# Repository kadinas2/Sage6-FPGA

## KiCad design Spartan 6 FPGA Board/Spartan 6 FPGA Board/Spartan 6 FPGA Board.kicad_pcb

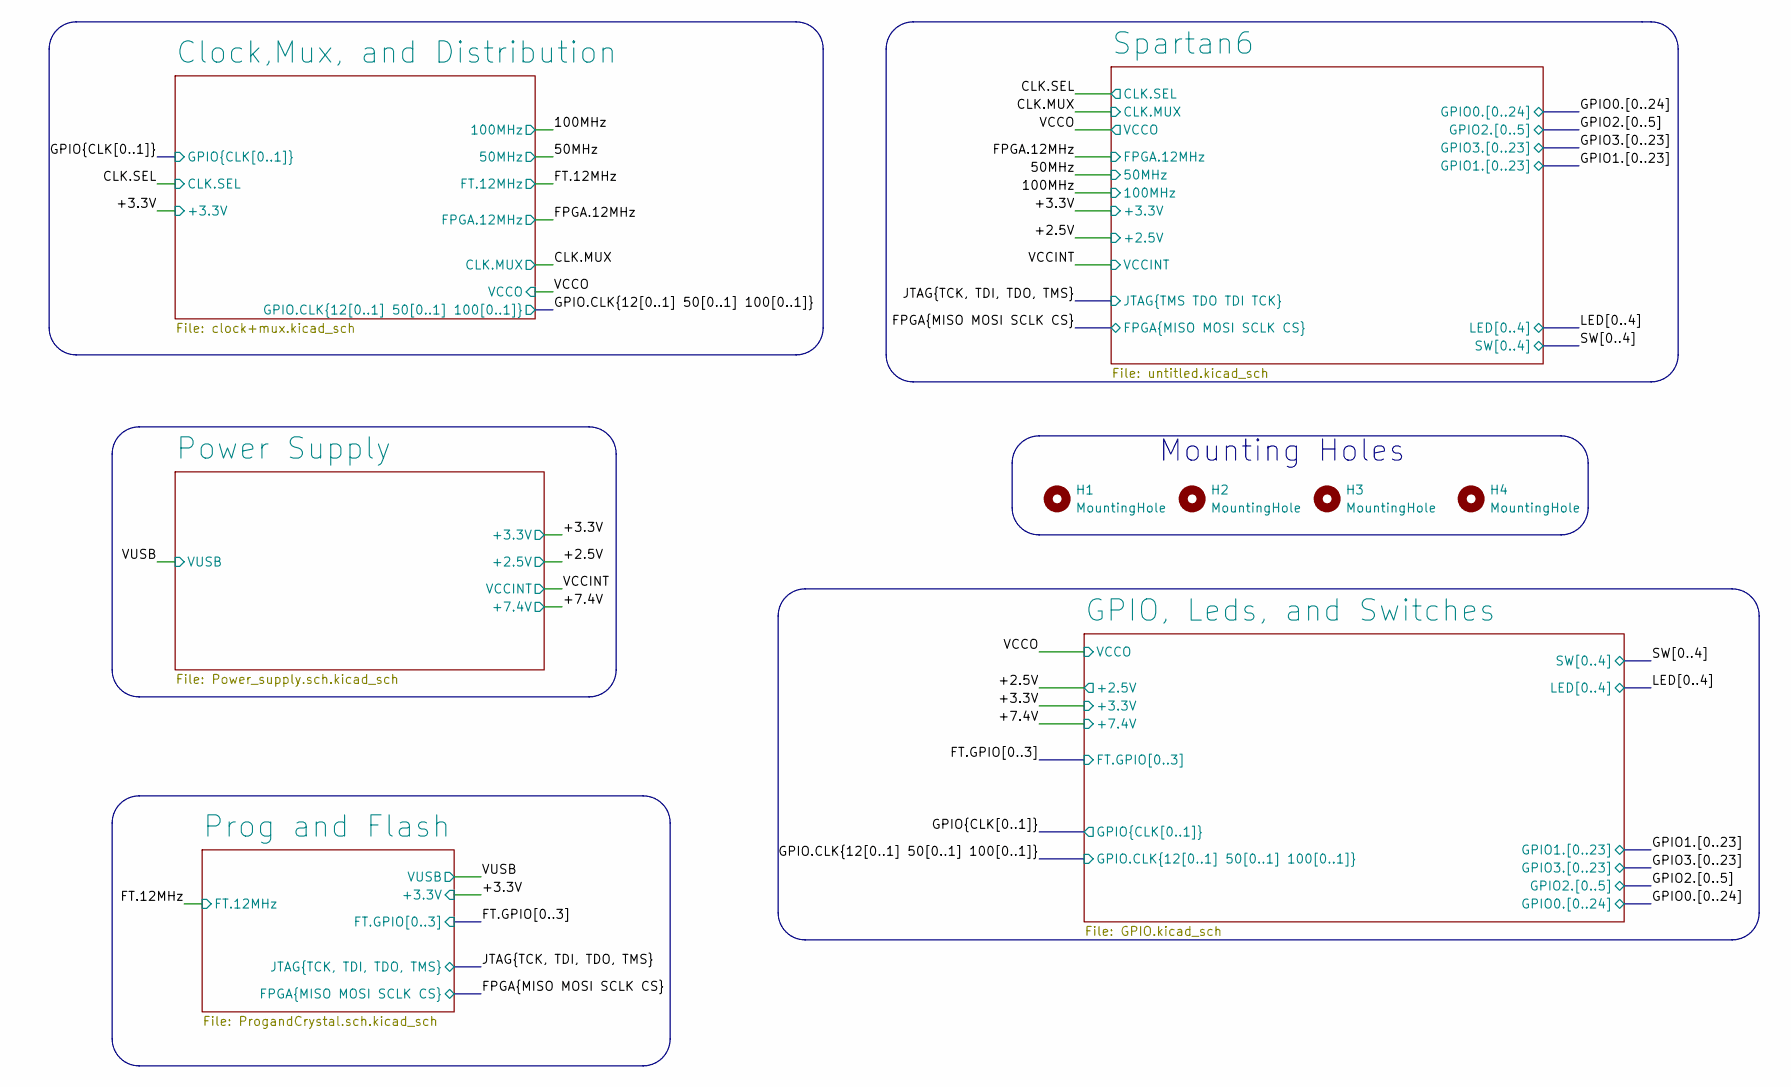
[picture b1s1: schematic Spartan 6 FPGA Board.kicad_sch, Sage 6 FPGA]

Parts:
H1, H2, H3, H4: MountingHole; MountingHole_2.2mm_M2

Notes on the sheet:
Mounting Holes

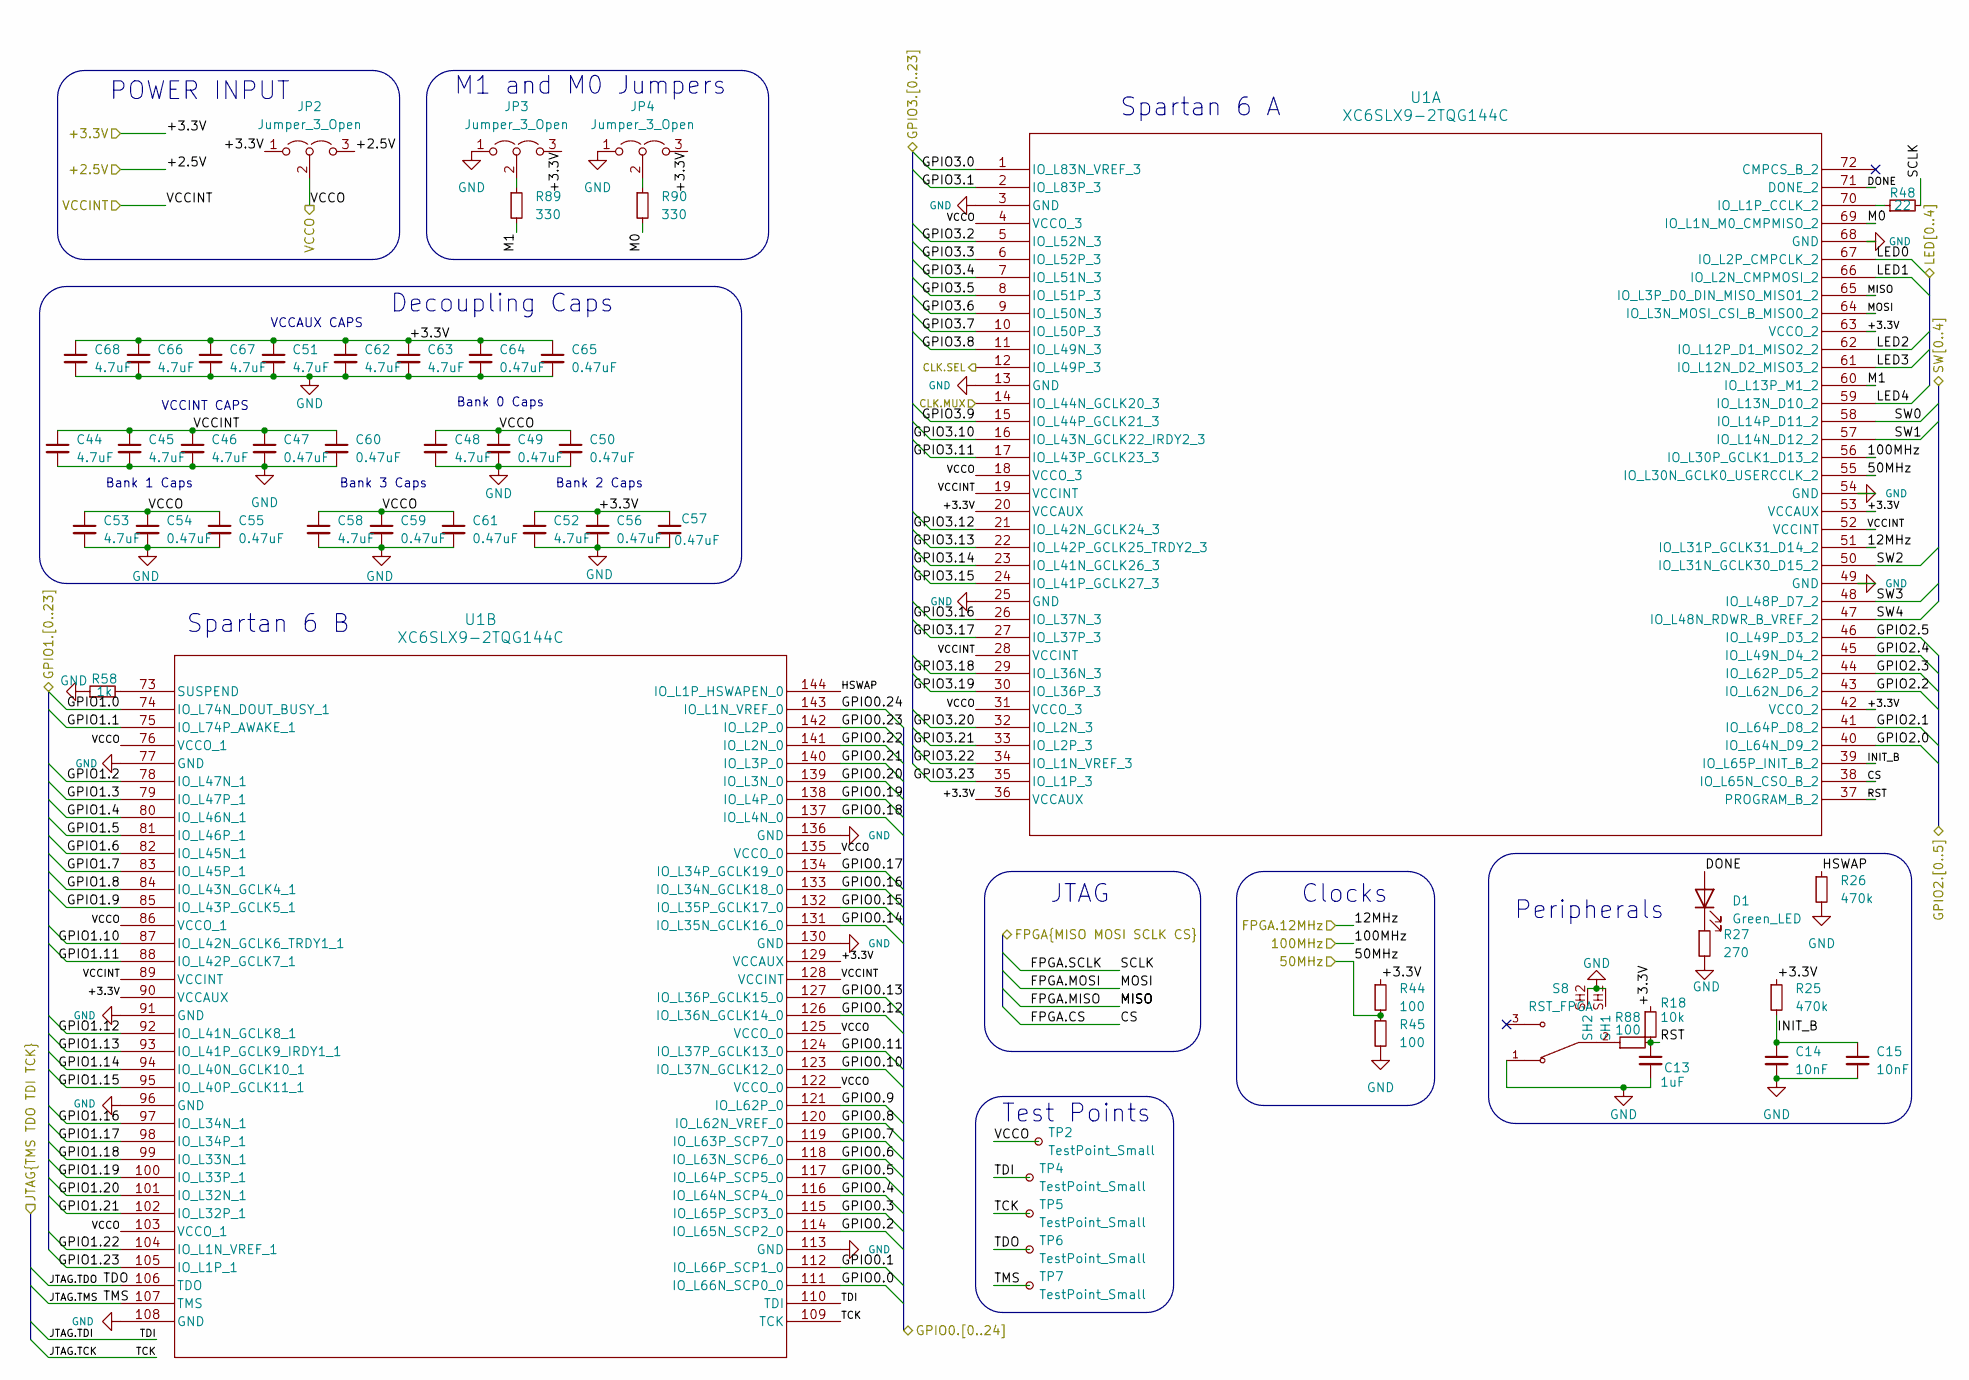
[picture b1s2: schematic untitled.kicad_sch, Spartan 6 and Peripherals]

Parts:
C13: 1uF; C_0805_2012Metric_Pad1.18x1.45mm_HandSolder
C14, C15: 10nF; C_0805_2012Metric_Pad1.18x1.45mm_HandSolder
C44, C45, C46, C48, C51, C52, C53, C58, C62, C63, C66, C67, C68: 4.7uF; C_0805_2012Metric_Pad1.18x1.45mm_HandSolder
C47, C49, C50, C54, C55, C56, C57, C59, C60, C61, C64, C65: 0.47uF; C_0805_2012Metric_Pad1.18x1.45mm_HandSolder
D1: Green_LED; LED_0805_2012Metric
JP2, JP3, JP4: Jumper_3_Open; PinHeader_1x03_P2.54mm_Vertical
R18: 10k; R_0805_2012Metric_Pad1.20x1.40mm_HandSolder
R25, R26: 470k; R_0805_2012Metric_Pad1.20x1.40mm_HandSolder
R27: 270; R_0805_2012Metric_Pad1.20x1.40mm_HandSolder
R44, R45, R88: 100; R_0805_2012Metric_Pad1.20x1.40mm_HandSolder
R48: 22; R_0805_2012Metric_Pad1.20x1.40mm_HandSolder
R58: 1k; R_0805_2012Metric_Pad1.20x1.40mm_HandSolder
R89, R90: 330; R_0805_2012Metric_Pad1.20x1.40mm_HandSolder
S8: RST_FPGA; SW_SLW-835636-3A-RA-N-D; PARTREV 1.01
TP2, TP4, TP5, TP6, TP7: TestPoint_Small; TestPoint_Pad_D1.0mm
U1: XC6SLX9-2TQG144C; TQG144_XIL

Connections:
/50MHz: R44.2, R45.1, U1.55 (IO_L30N_GCLK0_USERCCLK_2); also elsewhere on the board
/100MHz: U1.56 (IO_L30P_GCLK1_D13_2); also elsewhere on the board
/+2.5V: JP2.3 (B); also elsewhere on the board
/+3.3V: C51.1, C52.1, C56.1, C57.1, C62.1, C63.1, C64.1, C65.1, C66.1, C67.1, C68.1, JP2.1 (A), JP3.3 (B), JP4.3 (B), R18.1, R25.1, R44.1, U1.20 (VCCAUX), U1.36 (VCCAUX), U1.42 (VCCO_2), U1.53 (VCCAUX), U1.63 (VCCO_2), U1.90 (VCCAUX), U1.129 (VCCAUX); also elsewhere on the board
/CLK.MUX: U1.14 (IO_L44N_GCLK20_3); also elsewhere on the board
/CLK.SEL: U1.12 (IO_L49P_3); also elsewhere on the board
/FPGA.12MHz: U1.51 (IO_L31P_GCLK31_D14_2); also elsewhere on the board
/FPGA.CS: U1.38 (IO_L65N_CSO_B_2); also elsewhere on the board
/FPGA.MISO: U1.65 (IO_L3P_D0_DIN_MISO_MISO1_2); also elsewhere on the board
/FPGA.MOSI: U1.64 (IO_L3N_MOSI_CSI_B_MISO0_2); also elsewhere on the board
/FPGA.SCLK: R48.2; also elsewhere on the board
/GPIO0.0: U1.111 (IO_L66N_SCP0_0); also elsewhere on the board
/GPIO0.1: U1.112 (IO_L66P_SCP1_0); also elsewhere on the board
/GPIO0.2: U1.114 (IO_L65N_SCP2_0); also elsewhere on the board
/GPIO0.3: U1.115 (IO_L65P_SCP3_0); also elsewhere on the board
/GPIO0.4: U1.116 (IO_L64N_SCP4_0); also elsewhere on the board
/GPIO0.5: U1.117 (IO_L64P_SCP5_0); also elsewhere on the board
/GPIO0.6: U1.118 (IO_L63N_SCP6_0); also elsewhere on the board
/GPIO0.7: U1.119 (IO_L63P_SCP7_0); also elsewhere on the board
/GPIO0.8: U1.120 (IO_L62N_VREF_0); also elsewhere on the board
/GPIO0.9: U1.121 (IO_L62P_0); also elsewhere on the board
/GPIO0.10: U1.123 (IO_L37N_GCLK12_0); also elsewhere on the board
/GPIO0.11: U1.124 (IO_L37P_GCLK13_0); also elsewhere on the board
/GPIO0.12: U1.126 (IO_L36N_GCLK14_0); also elsewhere on the board
/GPIO0.13: U1.127 (IO_L36P_GCLK15_0); also elsewhere on the board
/GPIO0.14: U1.131 (IO_L35N_GCLK16_0); also elsewhere on the board
/GPIO0.15: U1.132 (IO_L35P_GCLK17_0); also elsewhere on the board
/GPIO0.16: U1.133 (IO_L34N_GCLK18_0); also elsewhere on the board
/GPIO0.17: U1.134 (IO_L34P_GCLK19_0); also elsewhere on the board
/GPIO0.18: U1.137 (IO_L4N_0); also elsewhere on the board
/GPIO0.19: U1.138 (IO_L4P_0); also elsewhere on the board
/GPIO0.20: U1.139 (IO_L3N_0); also elsewhere on the board
/GPIO0.21: U1.140 (IO_L3P_0); also elsewhere on the board
/GPIO0.22: U1.141 (IO_L2N_0); also elsewhere on the board
/GPIO0.23: U1.142 (IO_L2P_0); also elsewhere on the board
/GPIO0.24: U1.143 (IO_L1N_VREF_0); also elsewhere on the board
/GPIO1.0: U1.74 (IO_L74N_DOUT_BUSY_1); also elsewhere on the board
/GPIO1.1: U1.75 (IO_L74P_AWAKE_1); also elsewhere on the board
/GPIO1.2: U1.78 (IO_L47N_1); also elsewhere on the board
/GPIO1.3: U1.79 (IO_L47P_1); also elsewhere on the board
/GPIO1.4: U1.80 (IO_L46N_1); also elsewhere on the board
/GPIO1.5: U1.81 (IO_L46P_1); also elsewhere on the board
/GPIO1.6: U1.82 (IO_L45N_1); also elsewhere on the board
/GPIO1.7: U1.83 (IO_L45P_1); also elsewhere on the board
/GPIO1.8: U1.84 (IO_L43N_GCLK4_1); also elsewhere on the board
/GPIO1.9: U1.85 (IO_L43P_GCLK5_1); also elsewhere on the board
/GPIO1.10: U1.87 (IO_L42N_GCLK6_TRDY1_1); also elsewhere on the board
/GPIO1.11: U1.88 (IO_L42P_GCLK7_1); also elsewhere on the board
/GPIO1.12: U1.92 (IO_L41N_GCLK8_1); also elsewhere on the board
/GPIO1.13: U1.93 (IO_L41P_GCLK9_IRDY1_1); also elsewhere on the board
/GPIO1.14: U1.94 (IO_L40N_GCLK10_1); also elsewhere on the board
/GPIO1.15: U1.95 (IO_L40P_GCLK11_1); also elsewhere on the board
/GPIO1.16: U1.97 (IO_L34N_1); also elsewhere on the board
/GPIO1.17: U1.98 (IO_L34P_1); also elsewhere on the board
/GPIO1.18: U1.99 (IO_L33N_1); also elsewhere on the board
/GPIO1.19: U1.100 (IO_L33P_1); also elsewhere on the board
/GPIO1.20: U1.101 (IO_L32N_1); also elsewhere on the board
/GPIO1.21: U1.102 (IO_L32P_1); also elsewhere on the board
/GPIO1.22: U1.104 (IO_L1N_VREF_1); also elsewhere on the board
/GPIO1.23: U1.105 (IO_L1P_1); also elsewhere on the board
/GPIO2.0: U1.40 (IO_L64N_D9_2); also elsewhere on the board
/GPIO2.1: U1.41 (IO_L64P_D8_2); also elsewhere on the board
/GPIO2.2: U1.43 (IO_L62N_D6_2); also elsewhere on the board
/GPIO2.3: U1.44 (IO_L62P_D5_2); also elsewhere on the board
/GPIO2.4: U1.45 (IO_L49N_D4_2); also elsewhere on the board
/GPIO2.5: U1.46 (IO_L49P_D3_2); also elsewhere on the board
/GPIO3.0: U1.1 (IO_L83N_VREF_3); also elsewhere on the board
/GPIO3.1: U1.2 (IO_L83P_3); also elsewhere on the board
/GPIO3.2: U1.5 (IO_L52N_3); also elsewhere on the board
/GPIO3.3: U1.6 (IO_L52P_3); also elsewhere on the board
/GPIO3.4: U1.7 (IO_L51N_3); also elsewhere on the board
/GPIO3.5: U1.8 (IO_L51P_3); also elsewhere on the board
/GPIO3.6: U1.9 (IO_L50N_3); also elsewhere on the board
/GPIO3.7: U1.10 (IO_L50P_3); also elsewhere on the board
/GPIO3.8: U1.11 (IO_L49N_3); also elsewhere on the board
/GPIO3.9: U1.15 (IO_L44P_GCLK21_3); also elsewhere on the board
/GPIO3.10: U1.16 (IO_L43N_GCLK22_IRDY2_3); also elsewhere on the board
/GPIO3.11: U1.17 (IO_L43P_GCLK23_3); also elsewhere on the board
/GPIO3.12: U1.21 (IO_L42N_GCLK24_3); also elsewhere on the board
/GPIO3.13: U1.22 (IO_L42P_GCLK25_TRDY2_3); also elsewhere on the board
/GPIO3.14: U1.23 (IO_L41N_GCLK26_3); also elsewhere on the board
/GPIO3.15: U1.24 (IO_L41P_GCLK27_3); also elsewhere on the board
/GPIO3.16: U1.26 (IO_L37N_3); also elsewhere on the board
/GPIO3.17: U1.27 (IO_L37P_3); also elsewhere on the board
/GPIO3.18: U1.29 (IO_L36N_3); also elsewhere on the board
/GPIO3.19: U1.30 (IO_L36P_3); also elsewhere on the board
/GPIO3.20: U1.32 (IO_L2N_3); also elsewhere on the board
/GPIO3.21: U1.33 (IO_L2P_3); also elsewhere on the board
/GPIO3.22: U1.34 (IO_L1N_VREF_3); also elsewhere on the board
/GPIO3.23: U1.35 (IO_L1P_3); also elsewhere on the board
/JTAG.TCK: TP5.1, U1.109 (TCK); also elsewhere on the board
/JTAG.TDI: TP4.1, U1.110 (TDI); also elsewhere on the board
/JTAG.TDO: TP6.1, U1.106 (TDO); also elsewhere on the board
/JTAG.TMS: TP7.1, U1.107 (TMS); also elsewhere on the board
/LED0: U1.67 (IO_L2P_CMPCLK_2); also elsewhere on the board
/LED1: U1.66 (IO_L2N_CMPMOSI_2); also elsewhere on the board
/LED2: U1.62 (IO_L12P_D1_MISO2_2); also elsewhere on the board
/LED3: U1.61 (IO_L12N_D2_MISO3_2); also elsewhere on the board
/LED4: U1.59 (IO_L13N_D10_2); also elsewhere on the board
/SW0: U1.58 (IO_L14P_D11_2); also elsewhere on the board
/SW1: U1.57 (IO_L14N_D12_2); also elsewhere on the board
/SW2: U1.50 (IO_L31N_GCLK30_D15_2); also elsewhere on the board
/SW3: U1.48 (IO_L48P_D7_2); also elsewhere on the board
/SW4: U1.47 (IO_L48N_RDWR_B_VREF_2); also elsewhere on the board
/Spartan6/DONE: D1.2 (A), U1.71 (DONE_2)
/Spartan6/HSWAP: R26.1, U1.144 (IO_L1P_HSWAPEN_0)
/Spartan6/INIT_B: C14.1, C15.1, R25.2, U1.39 (IO_L65P_INIT_B_2)
/Spartan6/M0: R90.2, U1.69 (IO_L1N_M0_CMPMISO_2)
/Spartan6/M1: R89.2, U1.60 (IO_L13P_M1_2)
/Spartan6/RST: C13.1, R18.2, R88.2, U1.37 (PROGRAM_B_2)
/VCCINT: C44.1, C45.1, C46.1, C47.1, C60.1, U1.19 (VCCINT), U1.28 (VCCINT), U1.52 (VCCINT), U1.89 (VCCINT), U1.128 (VCCINT); also elsewhere on the board
/VCCO: C48.1, C49.1, C50.1, C53.1, C54.1, C55.1, C58.1, C59.1, C61.1, JP2.2 (C), TP2.1, U1.4 (VCCO_3), U1.18 (VCCO_3), U1.31 (VCCO_3), U1.76 (VCCO_1), U1.86 (VCCO_1), U1.103 (VCCO_1), U1.122 (VCCO_0), U1.125 (VCCO_0), U1.135 (VCCO_0); also elsewhere on the board
GND: C13.2, C14.2, C15.2, C44.2, C45.2, C46.2, C47.2, C48.2, C49.2, C50.2, C51.2, C52.2, C53.2, C54.2, C55.2, C56.2, C57.2, C58.2, C59.2, C60.2, C61.2, C62.2, C63.2, C64.2, C65.2, C66.2, C67.2, C68.2, JP3.1 (A), JP4.1 (A), R26.2, R27.2, R45.2, R58.1, S8.1, S8.SH1, S8.SH2, U1.3 (GND), U1.13 (GND), U1.25 (GND), U1.49 (GND), U1.54 (GND), U1.68 (GND), U1.77 (GND), U1.91 (GND), U1.96 (GND), U1.108 (GND), U1.113 (GND), U1.130 (GND), U1.136 (GND); also elsewhere on the board
unnamed: D1.1 (K), R27.1
unnamed: JP3.2 (C), R89.1
unnamed: JP4.2 (C), R90.1
unnamed: R88.1, S8.2
unnamed: R48.1, U1.70 (IO_L1P_CCLK_2)
unnamed: R58.2, U1.73 (SUSPEND)

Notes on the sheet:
POWER INPUT
VCCAUX CAPS
Test Points
Peripherals
Bank 0 Caps
Bank 2 Caps
Bank 1 Caps
Bank 3 Caps
Decoupling Caps
Spartan 6 A
M1 and M0 Jumpers
VCCINT CAPS
Spartan 6 B
Clocks
JTAG

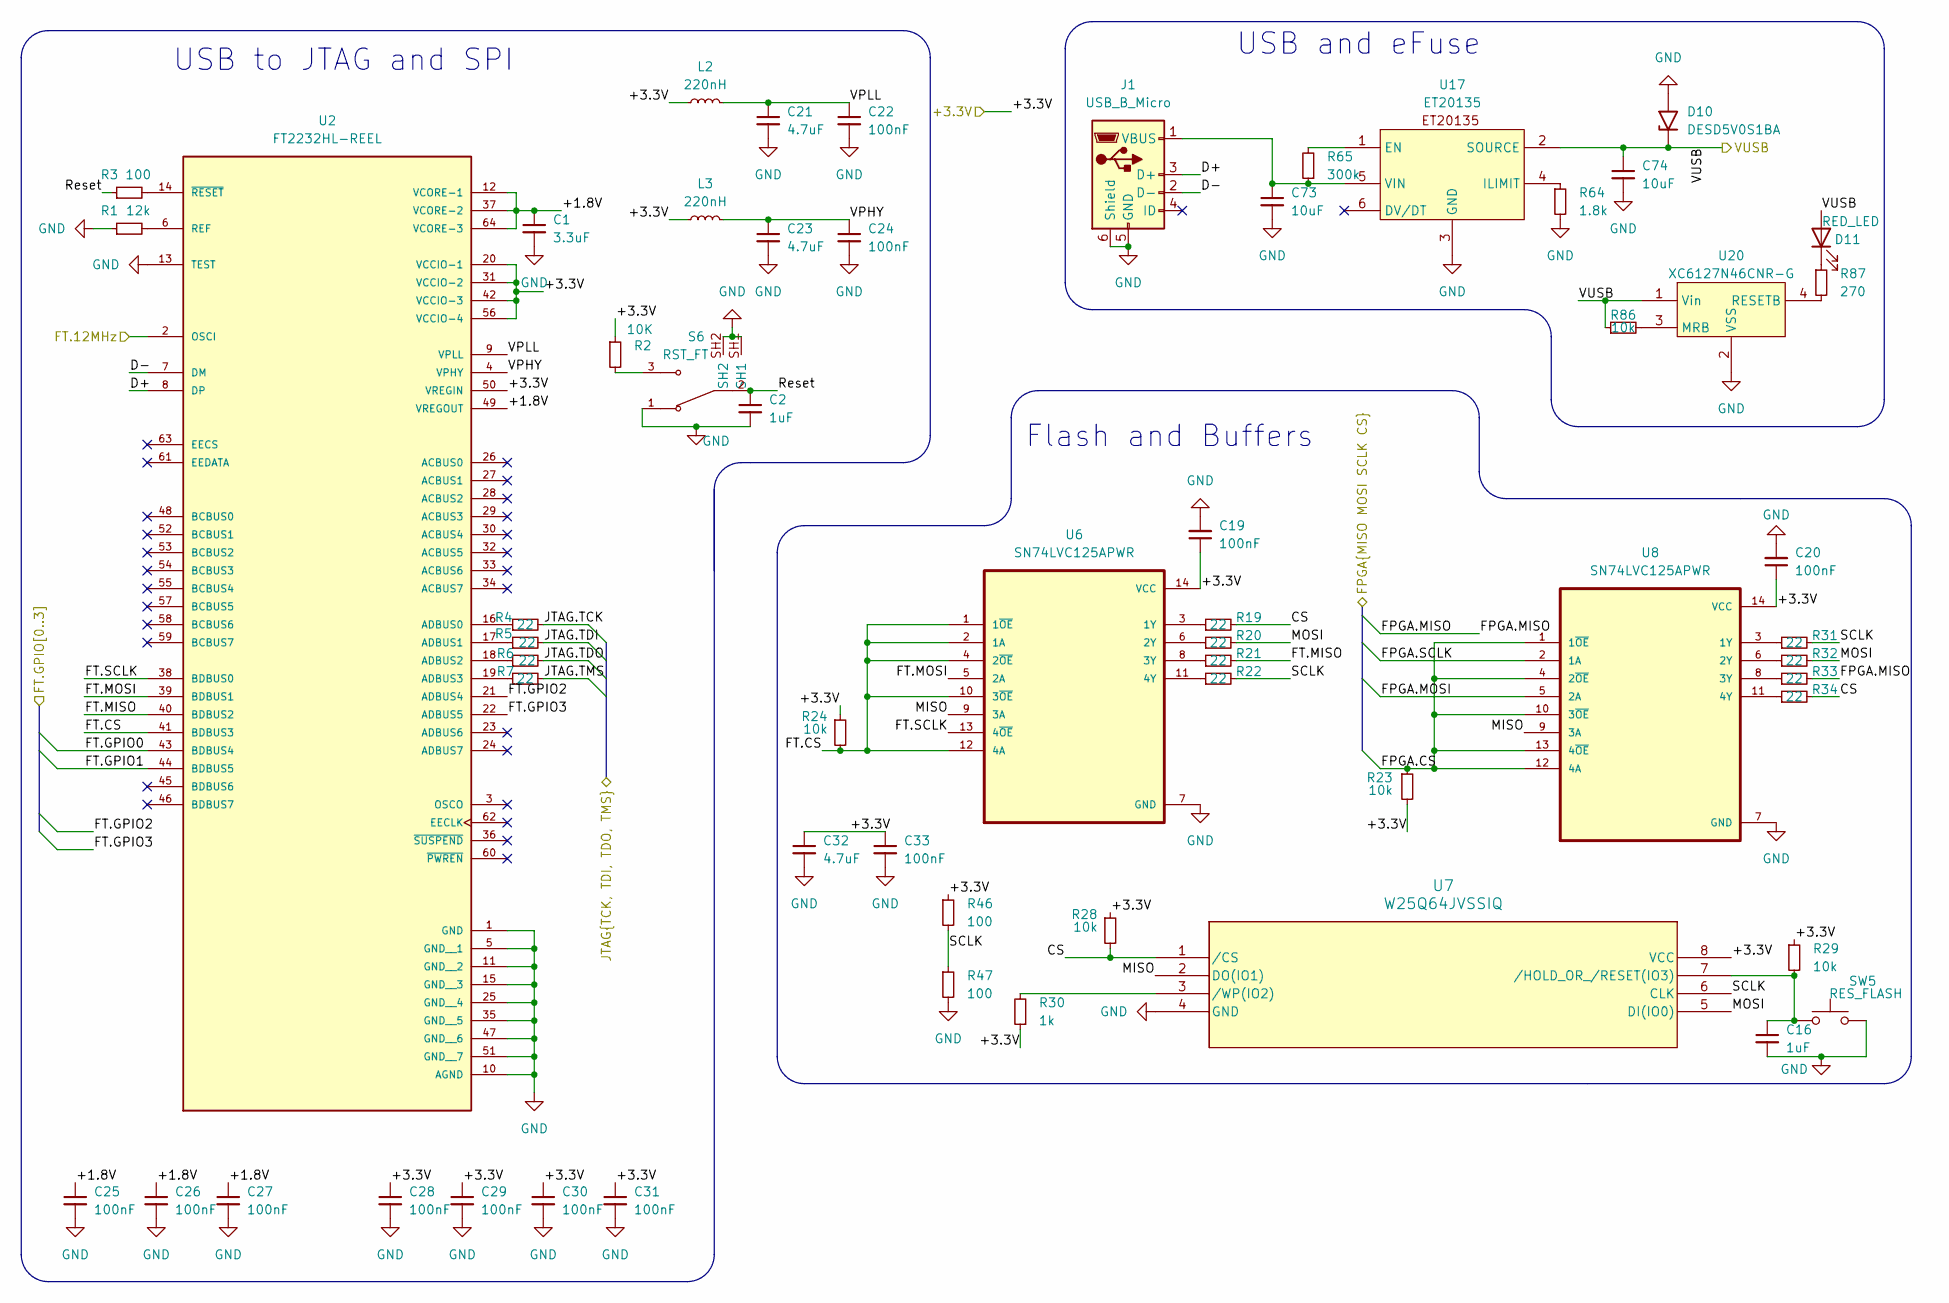
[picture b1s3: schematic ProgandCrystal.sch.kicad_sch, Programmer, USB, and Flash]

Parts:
C1: 3.3uF; C_0805_2012Metric_Pad1.18x1.45mm_HandSolder
C2, C16: 1uF; C_0805_2012Metric_Pad1.18x1.45mm_HandSolder
C19, C20, C22, C24, C25, C26, C27, C28, C29, C30, C31, C33: 100nF; C_0805_2012Metric_Pad1.18x1.45mm_HandSolder
C21, C23, C32: 4.7uF; C_0805_2012Metric_Pad1.18x1.45mm_HandSolder
C73, C74: 10uF; C_0805_2012Metric_Pad1.18x1.45mm_HandSolder
D10: DESD5V0S1BA; D_SOD-323_HandSoldering
D11: RED_LED; LED_0805_2012Metric_Pad1.15x1.40mm_HandSolder
J1: USB_B_Micro; AMPHENOL_10118194-0001LF
L2, L3: 220nH; L_0806_2016Metric_Hand_Solder
R1: 12k; R_0805_2012Metric_Pad1.20x1.40mm_HandSolder
R2: 10K; R_0805_2012Metric_Pad1.20x1.40mm_HandSolder
R3, R46, R47: 100; R_0805_2012Metric_Pad1.20x1.40mm_HandSolder
R4, R5, R6, R7, R19, R20, R21, R22, R31, R32, R33, R34: 22; R_0805_2012Metric_Pad1.20x1.40mm_HandSolder
R23, R24, R28, R29, R86: 10k; R_0805_2012Metric_Pad1.20x1.40mm_HandSolder
R30: 1k; R_0805_2012Metric_Pad1.20x1.40mm_HandSolder
R64: 1.8k; R_0805_2012Metric_Pad1.20x1.40mm_HandSolder
R65: 300k; R_0805_2012Metric_Pad1.20x1.40mm_HandSolder
R87: 270; R_0805_2012Metric_Pad1.20x1.40mm_HandSolder
S6: RST_FT; SW_SLW-835636-3A-RA-N-D; PARTREV 1.01
SW5: RES_FLASH; PTS636SM43SMTR LFS
U2: FT2232HL-REEL; QFP50P1200X1200X160-64N
U6, U8: SN74LVC125APWR; SOP65P640X120-14N
U7: W25Q64JVSSIQ; SOIC-8_5P28X5P28_WIN
U17: ET20135; SOT-23-6_Handsoldering
U20: XC6127N46CNR-G; SuperSOT-4_handsolder

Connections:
/+3.3V: C19.1, C20.1, C28.1, C29.1, C30.1, C31.1, C32.1, C33.1, L2.1, L3.1, R2.1, R23.2, R24.1, R28.1, R29.1, R30.1, R46.1, U2.20 (VCCIO-1), U2.31 (VCCIO-2), U2.42 (VCCIO-3), U2.50 (VREGIN), U2.56 (VCCIO-4), U6.14 (VCC), U7.8 (VCC), U8.14 (VCC); also elsewhere on the board
/FPGA.CS: R23.1, U8.1 (1~OE), U8.4 (2~OE), U8.10 (3~OE), U8.12 (4A), U8.13 (4~OE); also elsewhere on the board
/FPGA.MISO: R33.2; also elsewhere on the board
/FPGA.MOSI: U8.5 (2A); also elsewhere on the board
/FPGA.SCLK: U8.2 (1A); also elsewhere on the board
/FT.12MHz: U2.2 (OSCI); also elsewhere on the board
/FT.GPIO0: U2.43 (BDBUS4); also elsewhere on the board
/FT.GPIO1: U2.44 (BDBUS5); also elsewhere on the board
/FT.GPIO2: U2.21 (ADBUS4); also elsewhere on the board
/FT.GPIO3: U2.22 (ADBUS5); also elsewhere on the board
/JTAG.TCK: R4.2; also elsewhere on the board
/JTAG.TDI: R5.2; also elsewhere on the board
/JTAG.TDO: R6.2; also elsewhere on the board
/JTAG.TMS: R7.2; also elsewhere on the board
/Prog and Flash/+1.8V: C1.1, C25.1, C26.1, C27.1, U2.12 (VCORE-1), U2.37 (VCORE-2), U2.49 (VREGOUT), U2.64 (VCORE-3)
/Prog and Flash/CS: R19.2, R28.2, R34.2, U7.1 (/CS)
/Prog and Flash/D+: J1.3 (D+), U2.8 (DP)
/Prog and Flash/D-: J1.2 (D-), U2.7 (DM)
/Prog and Flash/FT.CS: R24.2, U2.41 (BDBUS3), U6.1 (1~OE), U6.2 (1A), U6.4 (2~OE), U6.10 (3~OE), U6.12 (4A)
/Prog and Flash/FT.MISO: R21.2, U2.40 (BDBUS2)
/Prog and Flash/FT.MOSI: U2.39 (BDBUS1), U6.5 (2A)
/Prog and Flash/FT.SCLK: U2.38 (BDBUS0), U6.13 (4~OE)
/Prog and Flash/MISO: U6.9 (3A), U7.2 (DO(IO1)), U8.9 (3A)
/Prog and Flash/MOSI: R20.2, R32.2, U7.5 (DI(IO0))
/Prog and Flash/Reset: C2.1, R3.1, S6.2
/Prog and Flash/SCLK: R22.2, R31.2, R46.2, R47.1, U7.6 (CLK)
/Prog and Flash/VPHY: C23.1, C24.1, L3.2, U2.4 (VPHY)
/Prog and Flash/VPLL: C21.1, C22.1, L2.2, U2.9 (VPLL)
/VUSB: C74.1, D10.1 (A1), D11.2 (A), R86.1, U17.2 (SOURCE), U20.1 (Vin); also elsewhere on the board
GND: C1.2, C2.2, C16.2, C19.2, C20.2, C21.2, C22.2, C23.2, C24.2, C25.2, C26.2, C27.2, C28.2, C29.2, C30.2, C31.2, C32.2, C33.2, C73.2, C74.2, D10.2 (A2), J1.5 (GND), J1.6 (Shield), R1.1, R47.2, R64.2, S6.1, S6.SH1, S6.SH2, SW5.2, U2.1 (GND), U2.5 (GND__1), U2.10 (AGND), U2.11 (GND__2), U2.13 (TEST), U2.15 (GND__3), U2.25 (GND__4), U2.35 (GND__5), U2.47 (GND__6), U2.51 (GND__7), U6.7 (GND), U7.4 (GND), U8.7 (GND), U17.3 (GND), U20.2 (VSS); also elsewhere on the board
unnamed: D11.1 (K), R87.1
unnamed: C73.1, J1.1 (VBUS), R65.1, U17.5 (VIN)
unnamed: R2.2, S6.3
unnamed: R4.1, U2.16 (ADBUS0)
unnamed: R5.1, U2.17 (ADBUS1)
unnamed: R6.1, U2.18 (ADBUS2)
unnamed: R7.1, U2.19 (ADBUS3)
unnamed: R1.2, U2.6 (REF)
unnamed: R3.2, U2.14 (~RESET)
unnamed: R19.1, U6.3 (1Y)
unnamed: R20.1, U6.6 (2Y)
unnamed: R21.1, U6.8 (3Y)
unnamed: R22.1, U6.11 (4Y)
unnamed: C16.1, R29.2, SW5.1, U7.7 (/HOLD_OR_/RESET(IO3))
unnamed: R30.2, U7.3 (/WP(IO2))
unnamed: R31.1, U8.3 (1Y)
unnamed: R32.1, U8.6 (2Y)
unnamed: R33.1, U8.8 (3Y)
unnamed: R34.1, U8.11 (4Y)
unnamed: R65.2, U17.1 (EN)
unnamed: R64.1, U17.4 (ILIMIT)
unnamed: R86.2, U20.3 (MRB)
unnamed: R87.2, U20.4 (RESETB)

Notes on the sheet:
Flash and Buffers
USB and eFuse
USB to JTAG and SPI

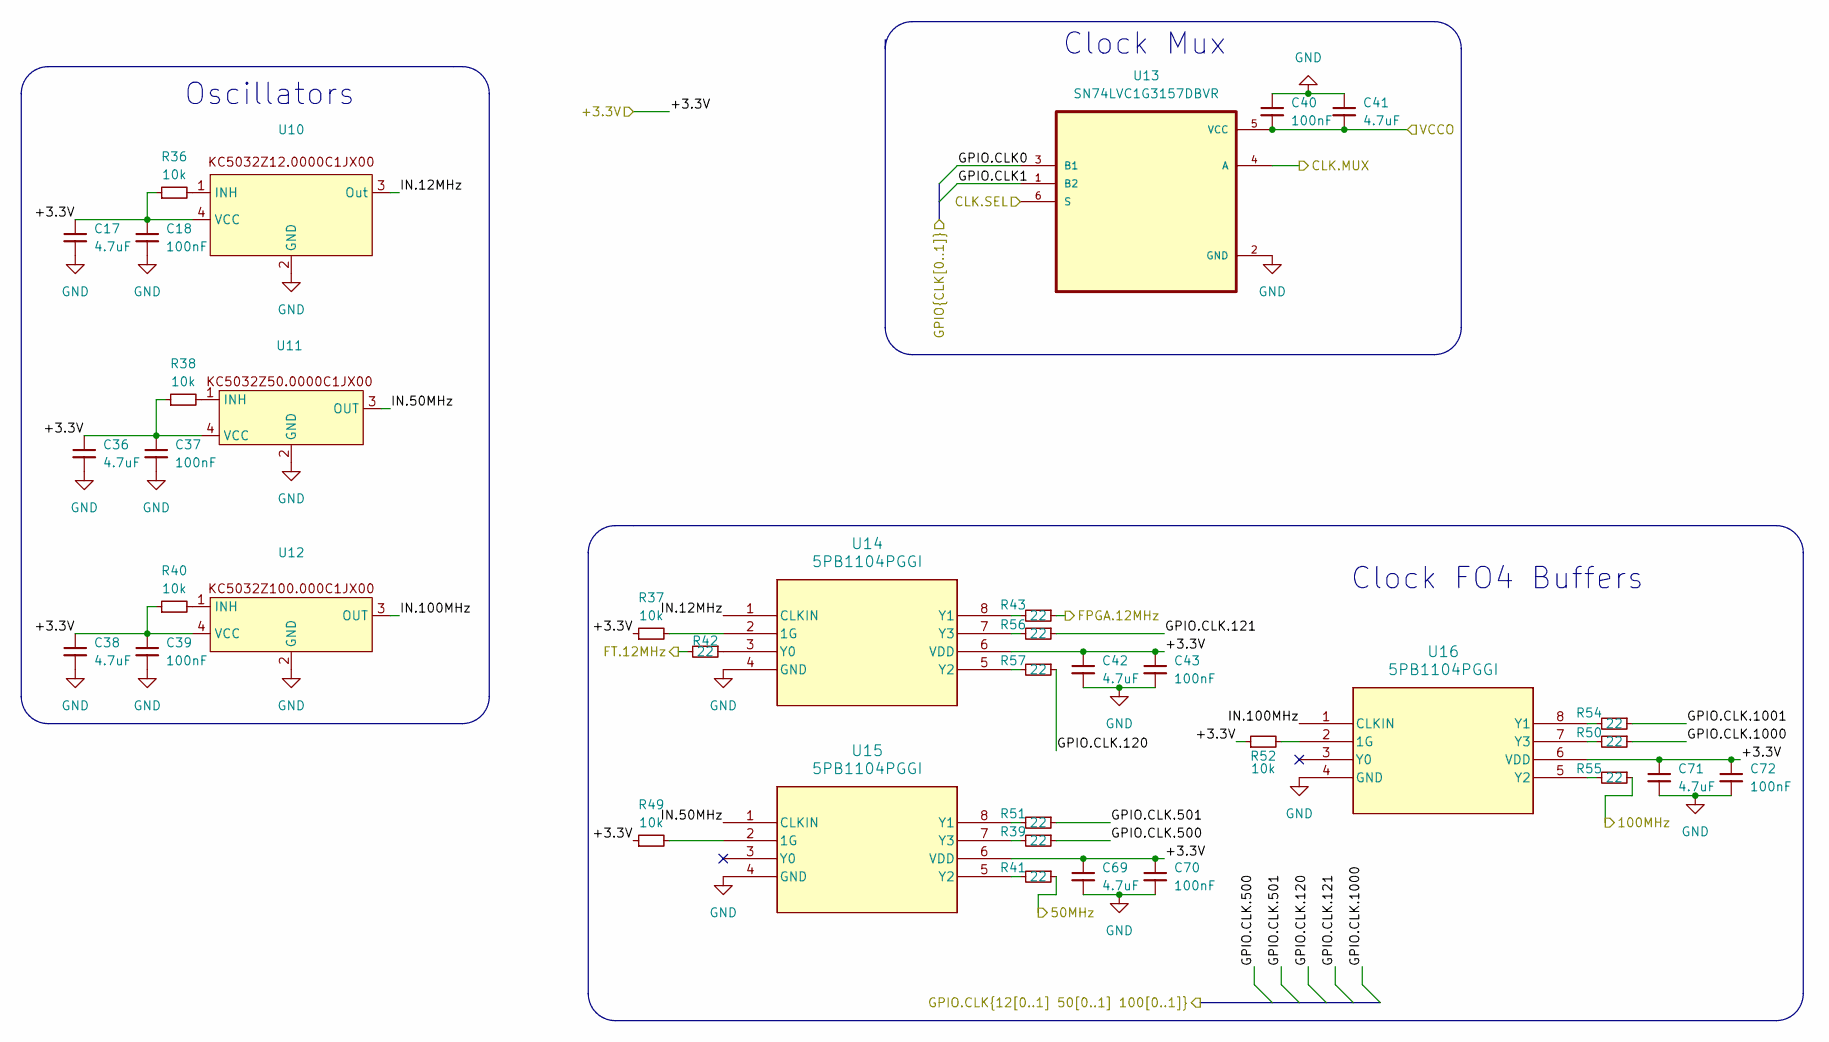
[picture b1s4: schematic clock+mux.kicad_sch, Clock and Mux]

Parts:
C17, C36, C38, C41, C42, C69, C71: 4.7uF; C_0805_2012Metric_Pad1.18x1.45mm_HandSolder
C18, C37, C39, C40, C43, C70, C72: 100nF; C_0805_2012Metric_Pad1.18x1.45mm_HandSolder
R36, R37, R38, R40, R49, R52: 10k; R_0805_2012Metric_Pad1.20x1.40mm_HandSolder
R39, R41, R42, R43, R50, R51, R54, R55, R56, R57: 22; R_0805_2012Metric_Pad1.20x1.40mm_HandSolder
U10, U11, U12: Oscillator_SMD_EuroQuartz_XO53-4Pin_5.0x3.2mm_HandSoldering
U13: SN74LVC1G3157DBVR; SOT95P280X145-6N
U14, U15, U16: 5PB1104PGGI; 5PB1102PGGI

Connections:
/50MHz: R41.1; also elsewhere on the board
/100MHz: R55.1; also elsewhere on the board
/+3.3V: C17.1, C18.1, C36.1, C37.1, C38.1, C39.1, C42.1, C43.1, C69.1, C70.1, C71.1, C72.1, R36.1, R37.1, R38.1, R40.1, R49.1, R52.1, U10.4 (VCC), U11.4 (VCC), U12.4 (VCC), U14.6 (VDD), U15.6 (VDD), U16.6 (VDD); also elsewhere on the board
/CLK.MUX: U13.4 (A); also elsewhere on the board
/CLK.SEL: U13.6 (S); also elsewhere on the board
/Clock,Mux, and Distribution/IN.12MHz: U10.3 (Out), U14.1 (CLKIN)
/Clock,Mux, and Distribution/IN.50MHz: U11.3 (OUT), U15.1 (CLKIN)
/Clock,Mux, and Distribution/IN.100MHz: U12.3 (OUT), U16.1 (CLKIN)
/FPGA.12MHz: R43.1; also elsewhere on the board
/FT.12MHz: R42.2; also elsewhere on the board
/GPIO.CLK0: U13.3 (B1); also elsewhere on the board
/GPIO.CLK1: U13.1 (B2); also elsewhere on the board
/GPIO.CLK.120: R57.1; also elsewhere on the board
/GPIO.CLK.121: R56.1; also elsewhere on the board
/GPIO.CLK.500: R39.1; also elsewhere on the board
/GPIO.CLK.501: R51.1; also elsewhere on the board
/GPIO.CLK.1000: R50.1; also elsewhere on the board
/GPIO.CLK.1001: R54.1; also elsewhere on the board
/VCCO: C40.2, C41.2, U13.5 (VCC); also elsewhere on the board
GND: C17.2, C18.2, C36.2, C37.2, C38.2, C39.2, C40.1, C41.1, C42.2, C43.2, C69.2, C70.2, C71.2, C72.2, U10.2 (GND), U11.2 (GND), U12.2 (GND), U13.2 (GND), U14.4 (GND), U15.4 (GND), U16.4 (GND); also elsewhere on the board
unnamed: R36.2, U10.1 (INH)
unnamed: R38.2, U11.1 (INH)
unnamed: R40.2, U12.1 (INH)
unnamed: R37.2, U14.2 (1G)
unnamed: R42.1, U14.3 (Y0)
unnamed: R43.2, U14.8 (Y1)
unnamed: R57.2, U14.5 (Y2)
unnamed: R56.2, U14.7 (Y3)
unnamed: R49.2, U15.2 (1G)
unnamed: R51.2, U15.8 (Y1)
unnamed: R41.2, U15.5 (Y2)
unnamed: R39.2, U15.7 (Y3)
unnamed: R52.2, U16.2 (1G)
unnamed: R54.2, U16.8 (Y1)
unnamed: R55.2, U16.5 (Y2)
unnamed: R50.2, U16.7 (Y3)

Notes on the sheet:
Clock Mux
Clock FO4 Buffers
Oscillators
